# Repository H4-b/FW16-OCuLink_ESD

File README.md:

# OCuLink 8i Expansion Board for the Framework 16

## The schematic

The schematic in itself is pretty simple. You only need to connect the TX and RX PCIe lanes to the correct pins of the OCuLink connector. And then add components such as the EEPROM that the Embedded Controller (EC) on the laptop reads to configure GPIO pins and bifurcation.

A pdf version of the schematic is available [here](./imgs/schematic.pdf).

### EEPROM
As for the EEPROM, I have decided to use the same one that Framework is using in their [Dual SSD reference design](https://github.com/FrameworkComputer/ExpansionBay/tree/main/Dual%20SSD%20Reference%20Design). The `BR24G32FVT-3GE2`. The chip is marked as not recommended for new design according to Mouser, but it still seems to be in stock, although it can easily be swapped with another if required.

The EEPROM's address pins are all connected to the ground as that is the address the EC expects and by default the write protection (WP) is disabled by being connected to GND to allow writing data to it.

### Fans
For the fans I had to go with an alternative FPC header, as the one Framework uses on their boards was not available anywhere. The connector I use is slightly smaller, but still makes the connection nevertheless and the fans do spin up. I have specifically went with the [`AFC05-S04FIA-00`](https://www.lcsc.com/product-detail/C561383.html) that is available on LCSC to use with JLCPCB's assembly.

## Firmware
The firmware file is generated using [Framework's Expansion Bay tool](https://github.com/FrameworkComputer/ExpansionBayConfigurationGenerator). More info on the specific file I have been using in my testing and how I flashed it *SOON*.

## The PCB layout

For the layout I have went with a 4-layer board and did manage to successfully stay within JLCPCB's fabrication limits. For the production runs I have done a 1.2mm ENIG board and used the JLC04121H-7628 stackup.

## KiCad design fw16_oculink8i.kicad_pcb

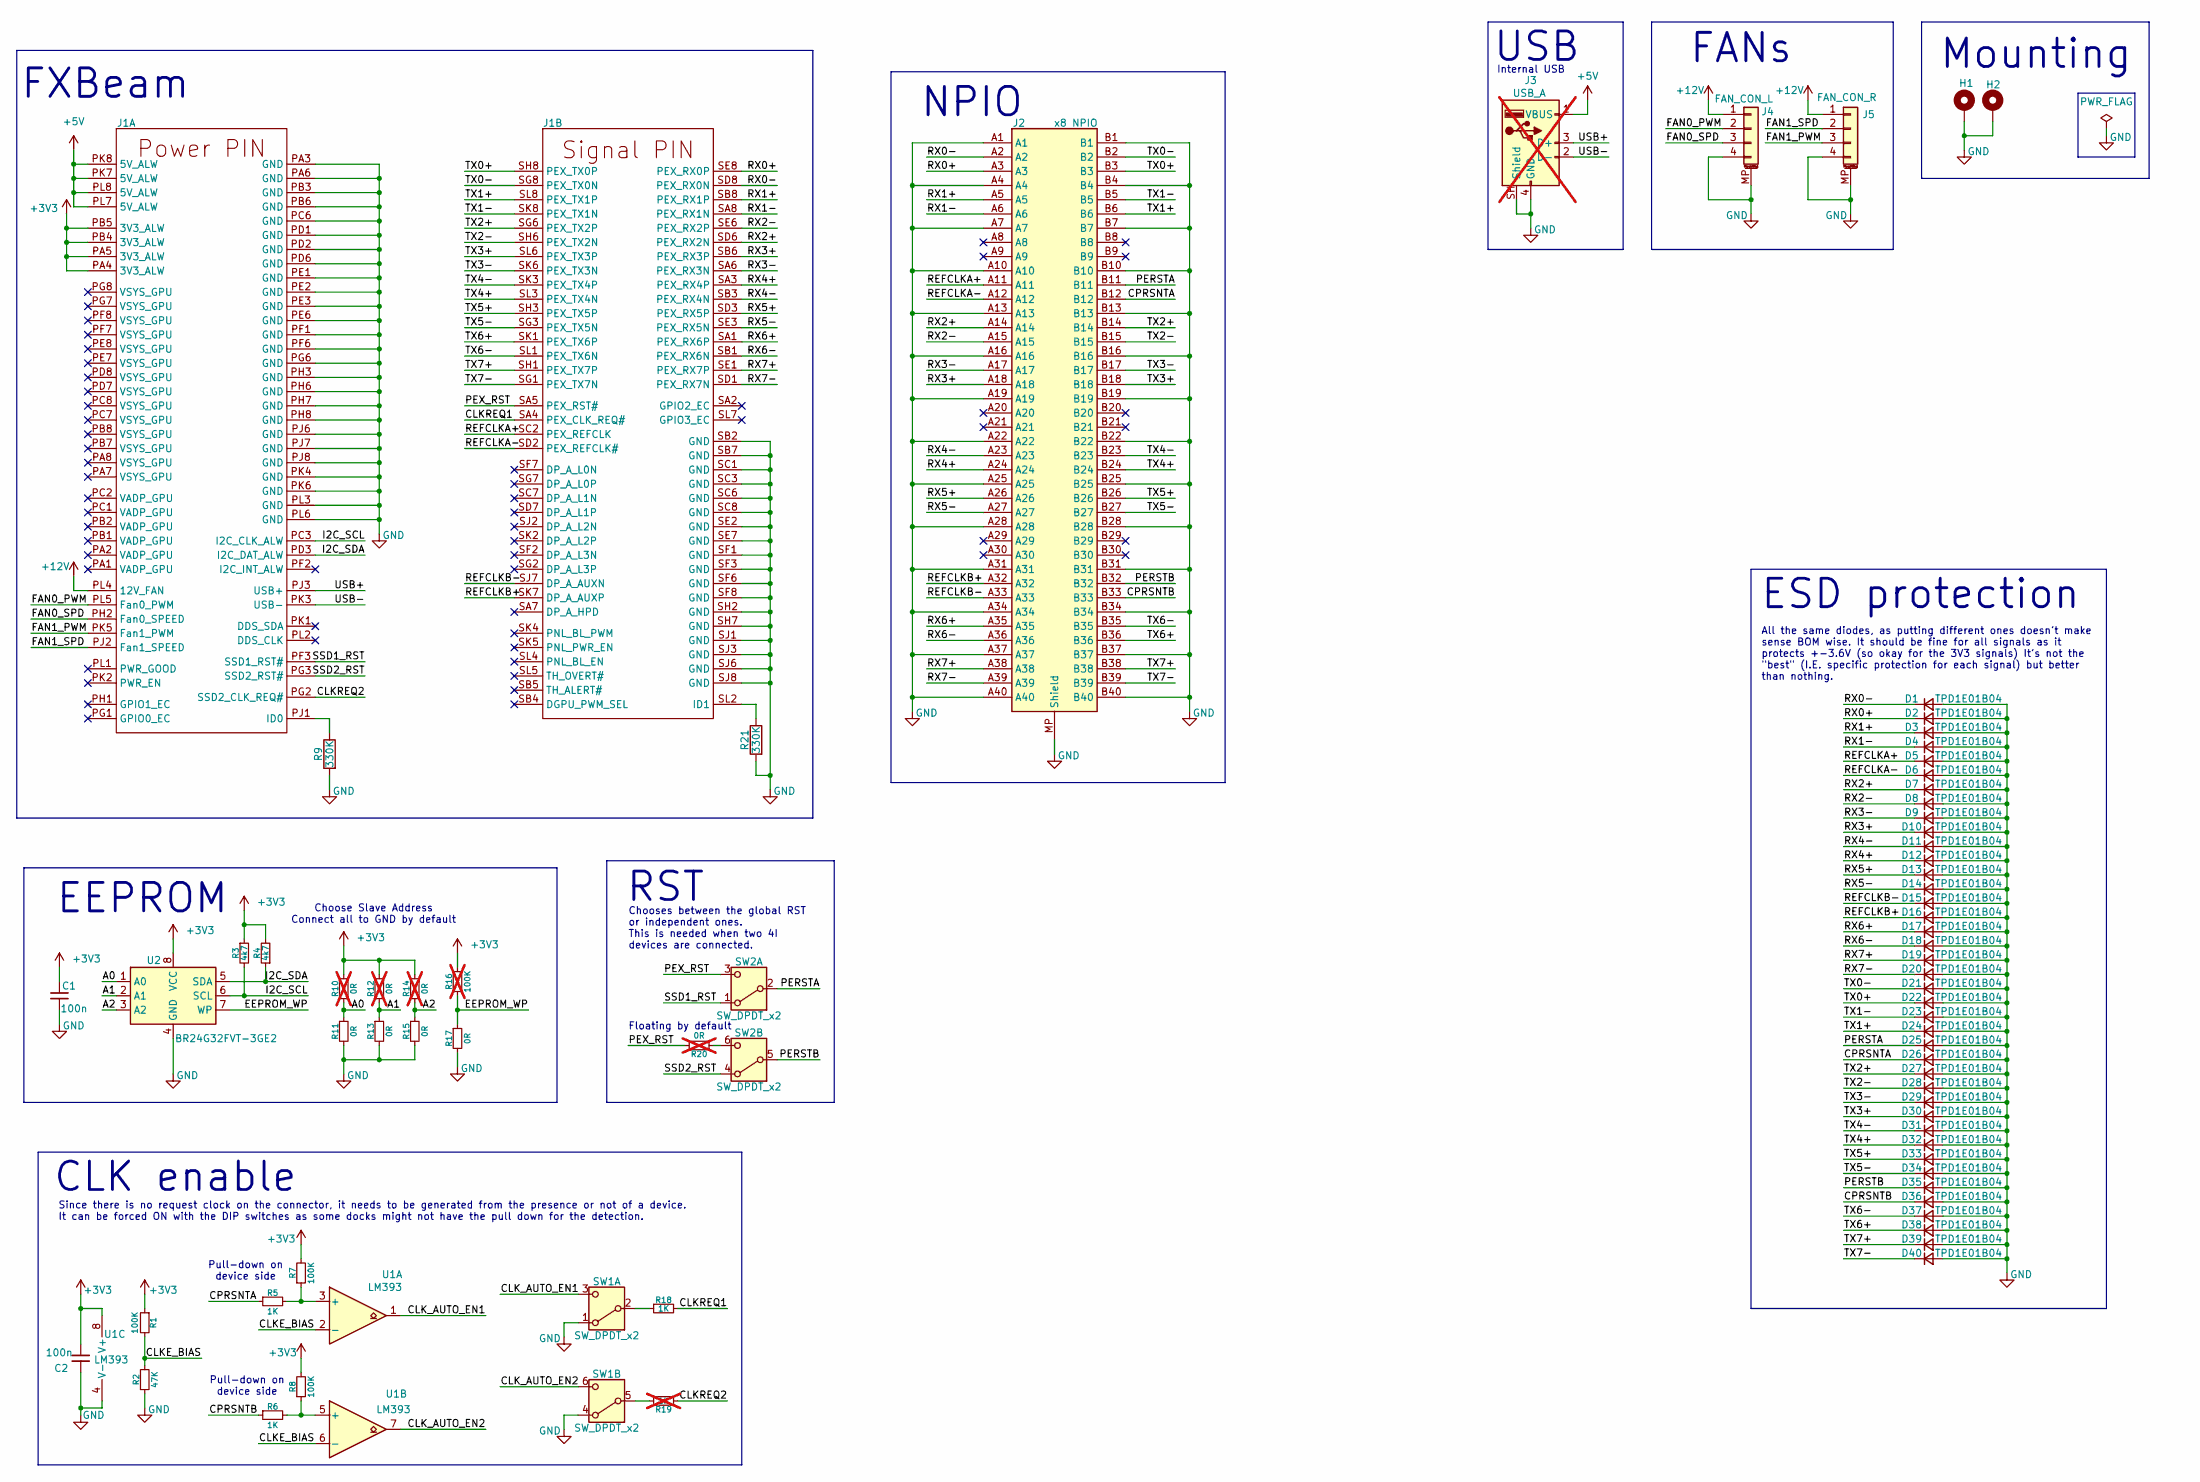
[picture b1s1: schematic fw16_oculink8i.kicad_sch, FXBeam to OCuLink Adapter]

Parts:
C1, C2: 100n; C_0402_1005Metric
D1, D2, D3, D4, D5, D6, D7, D8, D9, D10, D11, D12, D13, D14, D15, D16, D17, D18, D19, D20, D21, D22, D23, D24, D25, D26, D27, D28, D29, D30, D31, D32, D33, D34, D35, D36, D37, D38, D39, D40: TPD1E01B04; Texas_DPY0002A_0.6x1mm_P0.65mm
H1, H2: MountingHole_Pad; MountingHole_6.2mm_EasySolder_Cut
J1: FXBeam
J2: x8 NPIO; Nano-Pitch-173162-0132
J3: USB_A; 87583-2010BLF; not fitted
J4: FAN_CON_L; AFC58-S04FIA_4Pin
J5: FAN_CON_R; AFC58-S04FIA_4Pin
R1, R7, R8: 100K; R_0402_1005Metric
R2: 47K; R_0402_1005Metric
R3, R4: 4k7; R_0402_1005Metric; Tolerance 1%
R5, R6, R18: 1K; R_0402_1005Metric
R9, R21: 330K; R_0402_1005Metric; Tolerance 1%
R10, R12, R14, R20: 0R; R_0402_1005Metric; not fitted
R11, R13, R15, R17: 0R; R_0402_1005Metric
R16: 100K; R_0402_1005Metric; Tolerance 1%; not fitted
R19: 1K; R_0402_1005Metric; not fitted
SW1, SW2: SW_DPDT_x2; SSSS820101
U1: LM393; SOIC-8_3.9x4.9mm_P1.27mm
U2: BR24G32FVT-3GE2; TSSOP-8_4.4x3mm_P0.65mm

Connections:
+3V3: C1.1, C2.2, J1.PA4 (3V3_ALW), J1.PA5 (3V3_ALW), J1.PB4 (3V3_ALW), J1.PB5 (3V3_ALW), R1.1, R3.1, R4.2, R7.2, R8.2, R10.1, R12.1, R14.1, R16.1, U1.8 (V+), U2.8 (VCC)
+5V: J1.PK7 (5V_ALW), J1.PK8 (5V_ALW), J1.PL7 (5V_ALW), J1.PL8 (5V_ALW), J3.1 (VBUS)
+12V: J1.PL4 (12V_FAN), J4.1, J5.1
/A0: R10.2, R11.1, U2.1 (A0)
/A1: R12.2, R13.1, U2.2 (A1)
/A2: R14.2, R15.1, U2.3 (A2)
/CLKE_BIAS: R1.2, R2.2, U1.2 (-), U1.6 (-)
/CLKREQ1: J1.SA4 (PEX_CLK_REQ#), R18.2
/CLKREQ2: J1.PG2 (SSD2_CLK_REQ#), R19.2
/CLK_AUTO_EN1: SW1.3 (C), U1.1
/CLK_AUTO_EN2: SW1.6 (C), U1.7
/CPRSNTA: D26.1 (K), J2.B12, R5.1
/CPRSNTB: D36.1 (K), J2.B33, R6.1
/EEPROM_WP: R16.2, R17.1, U2.7 (WP)
/FAN0_PWM: J1.PL5 (Fan0_PWM), J4.2
/FAN0_SPD: J1.PH2 (Fan0_SPEED), J4.3
/FAN1_PWM: J1.PK5 (Fan1_PWM), J5.3
/FAN1_SPD: J1.PJ2 (Fan1_SPEED), J5.2
/I2C_SCL: J1.PC3 (I2C_CLK_ALW), R3.2, U2.6 (SCL)
/I2C_SDA: J1.PD3 (I2C_DAT_ALW), R4.1, U2.5 (SDA)
/PERSTA: D25.1 (K), J2.B11, SW2.2 (B)
/PERSTB: D35.1 (K), J2.B32, SW2.5 (B)
/PEX_RST: J1.SA5 (PEX_RST#), R20.2, SW2.3 (C)
/REFCLKA+: D5.1 (K), J1.SC2 (PEX_REFCLK), J2.A11
/REFCLKA-: D6.1 (K), J1.SD2 (PEX_REFCLK#), J2.A12
/REFCLKB+: D16.1 (K), J1.SK7 (DP_A_AUXP), J2.A32
/REFCLKB-: D15.1 (K), J1.SJ7 (DP_A_AUXN), J2.A33
/RX0+: D2.1 (K), J1.SE8 (PEX_RX0P), J2.A3
/RX0-: D1.1 (K), J1.SD8 (PEX_RX0N), J2.A2
/RX1+: D3.1 (K), J1.SB8 (PEX_RX1P), J2.A5
/RX1-: D4.1 (K), J1.SA8 (PEX_RX1N), J2.A6
/RX2+: D7.1 (K), J1.SD6 (PEX_RX2N), J2.A14
/RX2-: D8.1 (K), J1.SE6 (PEX_RX2P), J2.A15
/RX3+: D10.1 (K), J1.SB6 (PEX_RX3P), J2.A18
/RX3-: D9.1 (K), J1.SA6 (PEX_RX3N), J2.A17
/RX4+: D12.1 (K), J1.SA3 (PEX_RX4P), J2.A24
/RX4-: D11.1 (K), J1.SB3 (PEX_RX4N), J2.A23
/RX5+: D13.1 (K), J1.SD3 (PEX_RX5P), J2.A26
/RX5-: D14.1 (K), J1.SE3 (PEX_RX5N), J2.A27
/RX6+: D17.1 (K), J1.SA1 (PEX_RX6P), J2.A35
/RX6-: D18.1 (K), J1.SB1 (PEX_RX6N), J2.A36
/RX7+: D19.1 (K), J1.SE1 (PEX_RX7P), J2.A38
/RX7-: D20.1 (K), J1.SD1 (PEX_RX7N), J2.A39
/SSD1_RST: J1.PF3 (SSD1_RST#), SW2.1 (A)
/SSD2_RST: J1.PG3 (SSD2_RST#), SW2.4 (A)
/TX0+: D22.1 (K), J1.SH8 (PEX_TX0P), J2.B3
/TX0-: D21.1 (K), J1.SG8 (PEX_TX0N), J2.B2
/TX1+: D24.1 (K), J1.SL8 (PEX_TX1P), J2.B6
/TX1-: D23.1 (K), J1.SK8 (PEX_TX1N), J2.B5
/TX2+: D27.1 (K), J1.SG6 (PEX_TX2P), J2.B14
/TX2-: D28.1 (K), J1.SH6 (PEX_TX2N), J2.B15
/TX3+: D30.1 (K), J1.SL6 (PEX_TX3P), J2.B18
/TX3-: D29.1 (K), J1.SK6 (PEX_TX3N), J2.B17
/TX4+: D32.1 (K), J1.SL3 (PEX_TX4N), J2.B24
/TX4-: D31.1 (K), J1.SK3 (PEX_TX4P), J2.B23
/TX5+: D33.1 (K), J1.SH3 (PEX_TX5P), J2.B26
/TX5-: D34.1 (K), J1.SG3 (PEX_TX5N), J2.B27
/TX6+: D38.1 (K), J1.SK1 (PEX_TX6P), J2.B36
/TX6-: D37.1 (K), J1.SL1 (PEX_TX6N), J2.B35
/TX7+: D39.1 (K), J1.SH1 (PEX_TX7P), J2.B38
/TX7-: D40.1 (K), J1.SG1 (PEX_TX7N), J2.B39
/USB+: J1.PJ3 (USB+), J3.3 (D+)
/USB-: J1.PK3 (USB-), J3.2 (D-)
GND: C1.2, C2.1, D1.2 (A), D2.2 (A), D3.2 (A), D4.2 (A), D5.2 (A), D6.2 (A), D7.2 (A), D8.2 (A), D9.2 (A), D10.2 (A), D11.2 (A), D12.2 (A), D13.2 (A), D14.2 (A), D15.2 (A), D16.2 (A), D17.2 (A), D18.2 (A), D19.2 (A), D20.2 (A), D21.2 (A), D22.2 (A), D23.2 (A), D24.2 (A), D25.2 (A), D26.2 (A), D27.2 (A), D28.2 (A), D29.2 (A), D30.2 (A), D31.2 (A), D32.2 (A), D33.2 (A), D34.2 (A), D35.2 (A), D36.2 (A), D37.2 (A), D38.2 (A), D39.2 (A), D40.2 (A), H1.1 (1_1), H2.1 (1_1), J1.PA3 (GND), J1.PA6 (GND), J1.PB3 (GND), J1.PB6 (GND), J1.PC6 (GND), J1.PD1 (GND), J1.PD2 (GND), J1.PD6 (GND), J1.PE1 (GND), J1.PE2 (GND), J1.PE3 (GND), J1.PE6 (GND), J1.PF1 (GND), J1.PF6 (GND), J1.PG6 (GND), J1.PH3 (GND), J1.PH6 (GND), J1.PH7 (GND), J1.PH8 (GND), J1.PJ6 (GND), J1.PJ7 (GND), J1.PJ8 (GND), J1.PK4 (GND), J1.PK6 (GND), J1.PL3 (GND), J1.PL6 (GND), J1.SB2 (GND), J1.SB7 (GND), J1.SC1 (GND), J1.SC3 (GND), J1.SC6 (GND), J1.SC8 (GND), J1.SE2 (GND), J1.SE7 (GND), J1.SF1 (GND), J1.SF3 (GND), J1.SF6 (GND), J1.SF8 (GND), J1.SH2 (GND), J1.SH7 (GND), J1.SJ1 (GND), J1.SJ3 (GND), J1.SJ6 (GND), J1.SJ8 (GND), J2.A1, J2.A4, J2.A7, J2.A10, J2.A13, J2.A16, J2.A19, J2.A22, J2.A25, J2.A28, J2.A31, J2.A34, J2.A37, J2.A40, J2.B1, J2.B4, J2.B7, J2.B10, J2.B13, J2.B16, J2.B19, J2.B22, J2.B25, J2.B28, J2.B31, J2.B34, J2.B37, J2.B40, J2.MP (Shield), J3.4 (GND), J3.SH (Shield), J4.4, J4.MP (MountPin), J5.4, J5.MP (MountPin), R2.1, R9.2, R11.2, R13.2, R15.2, R17.2, R21.2, SW1.1 (A), SW1.4 (A), U1.4 (V-), U2.4 (GND)
unnamed: J1.PJ1 (ID0), R9.1
unnamed: J1.SL2 (ID1), R21.1
unnamed: R18.1, SW1.2 (B)
unnamed: R19.1, SW1.5 (B)
unnamed: R20.1, SW2.6 (C)
unnamed: R5.2, R7.1, U1.3 (+)
unnamed: R6.2, R8.1, U1.5 (+)

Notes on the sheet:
NPIO
CLK enable
FANs
All the same diodes, as putting different ones doesn't make sense BOM wise. It should be fine for all signals as it protects +-3.6V (so okay for the 3V3 signals) It's not the "best" (I.E. specific protection for each signal) but better than nothing.
FXBeam
USB
RST
Choose Slave Address Connect all to GND by default
Pull-down on device side
Internal USB
Floating by default
Mounting
Chooses between the global RST or independent ones. This is needed when two 4I devices are connected.
ESD protection
EEPROM
Since there is no request clock on the connector, it needs to be generated from the presence or not of a device. It can be forced ON with the DIP switches as some docks might not have the pull down for the detection.

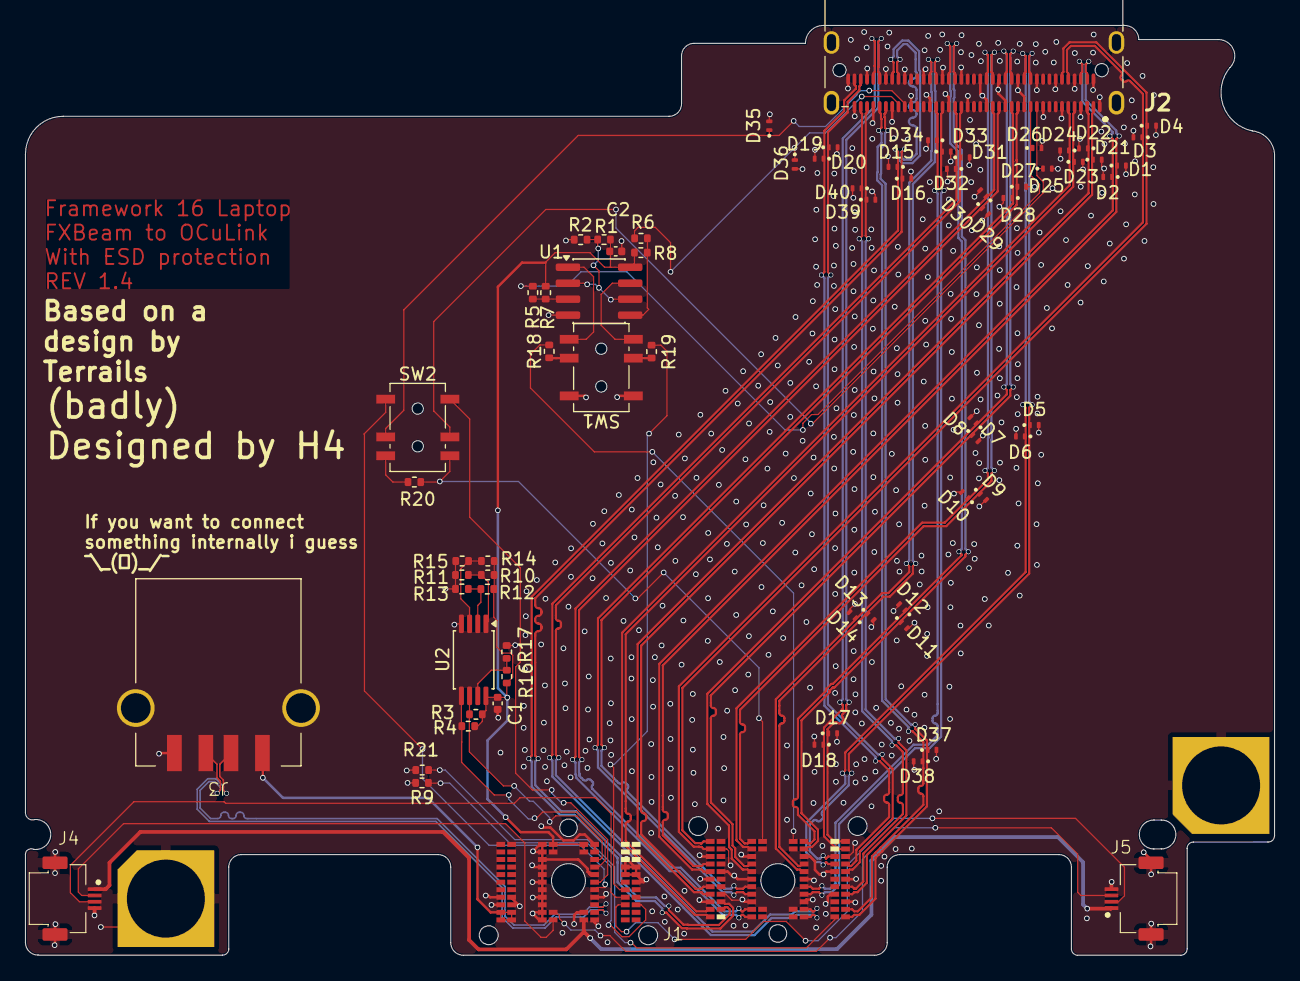
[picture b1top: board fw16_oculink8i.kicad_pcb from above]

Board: 4 copper layers, 99.3 x 73.9 mm, 74 parts (0 on the bottom side), 71 nets.
